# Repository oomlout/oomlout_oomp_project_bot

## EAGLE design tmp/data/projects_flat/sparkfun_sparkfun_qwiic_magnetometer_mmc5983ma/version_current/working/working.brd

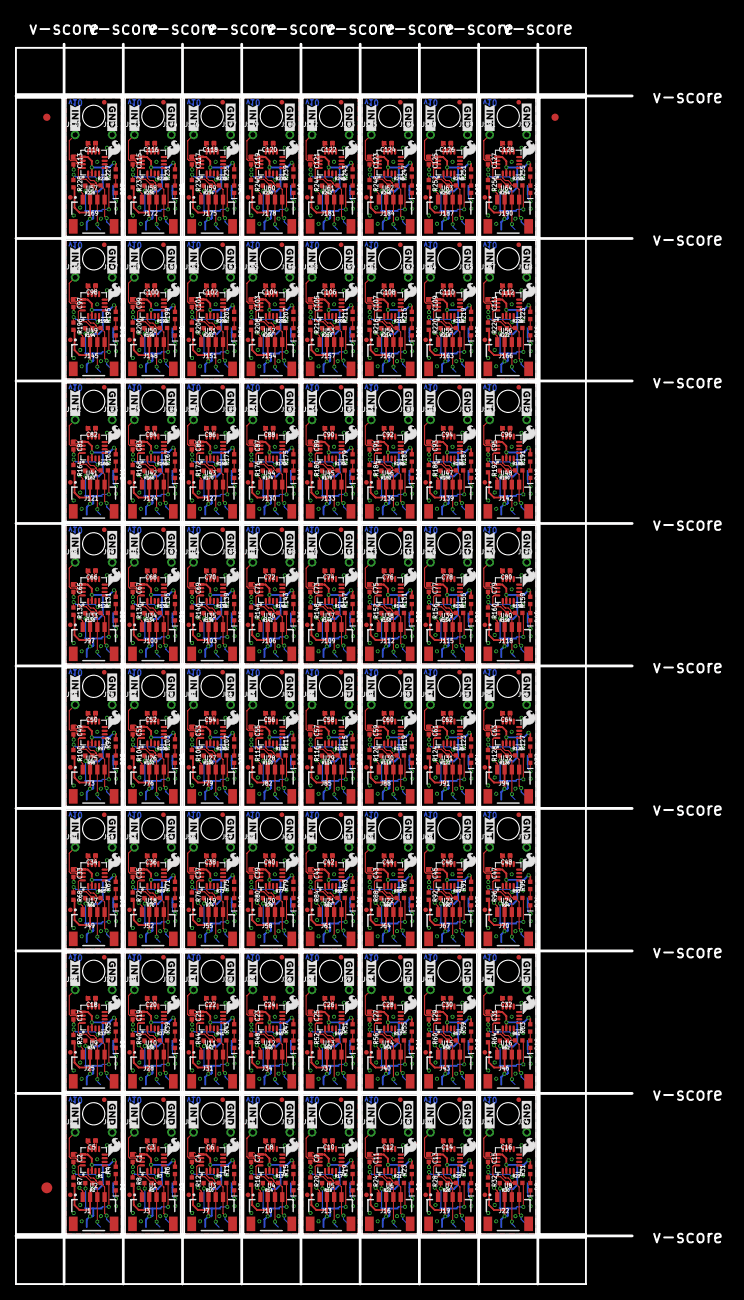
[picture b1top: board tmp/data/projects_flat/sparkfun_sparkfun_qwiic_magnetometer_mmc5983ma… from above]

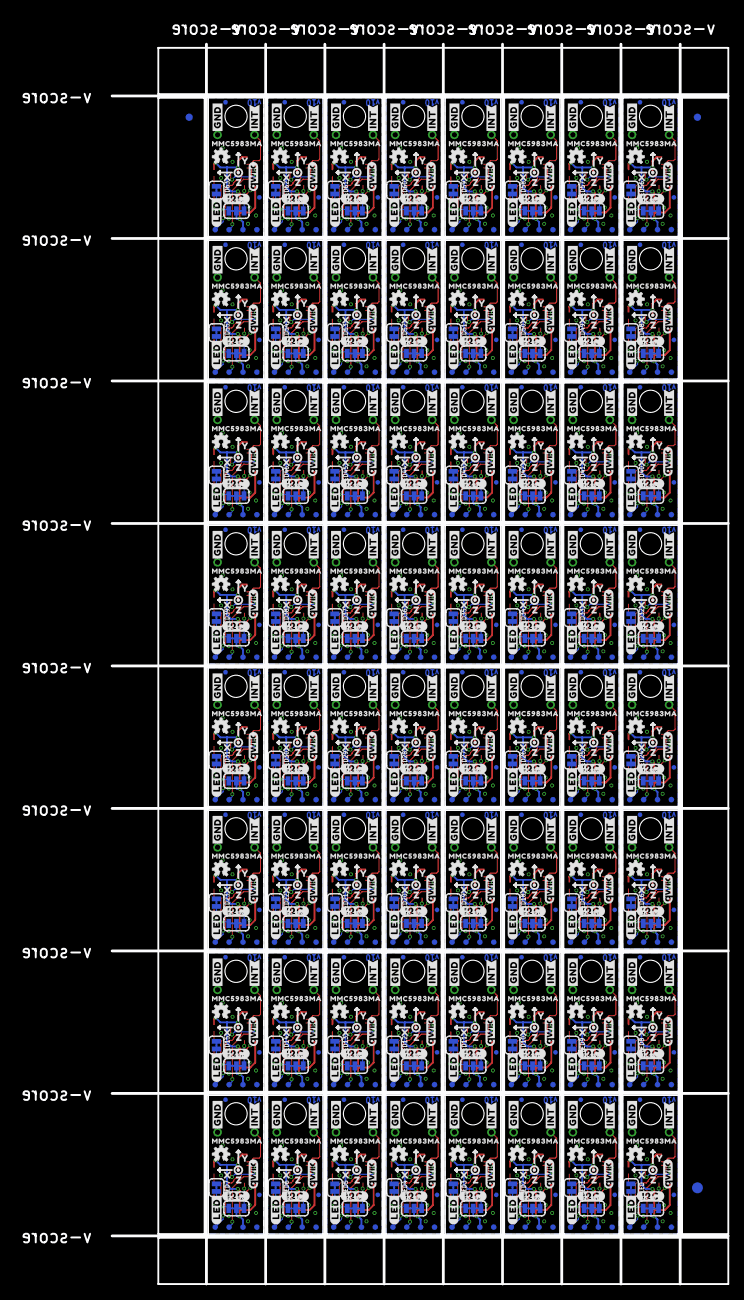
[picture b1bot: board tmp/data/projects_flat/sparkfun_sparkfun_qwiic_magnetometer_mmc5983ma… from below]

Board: 2 copper layers, 84.6 x 170.2 mm, 2374 parts (1155 on the bottom side), 704 nets.

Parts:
C1, C2, C4, C7, C9, C11, C13, C15, C17, C19, C21, C23, C25, C27, C29, C31, C33, C35, C37, C39, C41, C43, C45, C47, C49, C51, C53, C55, C57, C59, C61, C63, C65, C67, C69, C71, C73, C75, C77, C79, C81, C83, C85, C87, C89, C91, C93, C95, C97, C99, C101, C103, C105, C107, C109, C111, C113, C115, C117, C119, C121, C123, C125, C127: 1.0uF; 0402-TIGHT
C3, C5, C6, C8, C10, C12, C14, C16, C18, C20, C22, C24, C26, C28, C30, C32, C34, C36, C38, C40, C42, C44, C46, C48, C50, C52, C54, C56, C58, C60, C62, C64, C66, C68, C70, C72, C74, C76, C78, C80, C82, C84, C86, C88, C90, C92, C94, C96, C98, C100, C102, C104, C106, C108, C110, C112, C114, C116, C118, C120, C122, C124, C126, C128: 10uF; 0402-TIGHT
D1, D2, D3, D4, D5, D6, D7, D8, D9, D10, D11, D12, D13, D14, D15, D16, D17, D18, D19, D20, D21, D22, D23, D24, D25, D26, D27, D28, D29, D30, D31, D32, D33, D34, D35, D36, D37, D38, D39, D40, D41, D42, D43, D44, D45, D46, D47, D48, D49, D50, D51, D52, D53, D54, D55, D56, D57, D58, D59, D60, D61, D62, D63, D64: RED; LED-0402
E$1, E$2, E$3, E$4: FIDUCIAL-1X2
E$5, E$6: FIDUCIAL-1.5X3
FD1, FD2, FD3, FD4, FD5, FD6, FD7, FD8, FD9, FD10, FD11, FD12, FD13, FD14, FD15, FD16, FD17, FD18, FD19, FD20, FD21, FD22, FD23, FD24, FD25, FD26, FD27, FD28, FD29, FD30, FD31, FD32, FD33, FD34, FD35, FD36, FD37, FD38, FD39, FD40, FD41, FD42, FD43, FD44, FD45, FD46, FD47, FD48, FD49, FD50, FD51, FD52, FD53, FD54, FD55, FD56, FD57, FD58, FD59, FD60, FD61, FD62, FD63, FD64, FD65, FD66, FD67, FD68, FD69, FD70, FD71, FD72, FD73, FD74, FD75, FD76, FD77, FD78, FD79, FD80, FD81, FD82, FD83, FD84, FD85, FD86, FD87, FD88, FD89, FD90, FD91, FD92, FD93, FD94, FD95, FD96, FD97, FD98, FD99, FD100, FD101, FD102, FD103, FD104, FD105, FD106, FD107, FD108, FD109, FD110, FD111, FD112, FD113, FD114, FD115, FD116, FD117, FD118, FD119, FD120, FD121, FD122, FD123, FD124, FD125, FD126, FD127, FD128: FIDUCIALUFIDUCIAL; FIDUCIAL-MICRO
FID1, FID2, FID3, FID4, FID5, FID6, FID7, FID8, FID9, FID10, FID11, FID12, FID13, FID14, FID15, FID16, FID17, FID18, FID19, FID20, FID21, FID22, FID23, FID24, FID25, FID26, FID27, FID28, FID29, FID30, FID31, FID32, FID33, FID34, FID35, FID36, FID37, FID38, FID39, FID40, FID41, FID42, FID43, FID44, FID45, FID46, FID47, FID48, FID49, FID50, FID51, FID52, FID53, FID54, FID55, FID56, FID57, FID58, FID59, FID60, FID61, FID62, FID63, FID64, FID65, FID66, FID67, FID68, FID69, FID70, FID71, FID72, FID73, FID74, FID75, FID76, FID77, FID78, FID79, FID80, FID81, FID82, FID83, FID84, FID85, FID86, FID87, FID88, FID89, FID90, FID91, FID92, FID93, FID94, FID95, FID96, FID97, FID98, FID99, FID100, FID101, FID102, FID103, FID104, FID105, FID106, FID107, FID108, FID109, FID110, FID111, FID112, FID113, FID114, FID115, FID116, FID117, FID118, FID119, FID120, FID121, FID122, FID123, FID124, FID125, FID126, FID127, FID128: FIDUCIALUFIDUCIAL; FIDUCIAL-MICRO
FRAME1, FRAME2, FRAME3, FRAME4, FRAME5, FRAME6, FRAME7, FRAME8, FRAME9, FRAME10, FRAME11, FRAME12, FRAME13, FRAME14, FRAME15, FRAME16, FRAME17, FRAME18, FRAME19, FRAME20, FRAME21, FRAME22, FRAME23, FRAME24, FRAME25, FRAME26, FRAME27, FRAME28, FRAME29, FRAME30, FRAME31, FRAME32, FRAME33, FRAME34, FRAME35, FRAME36, FRAME37, FRAME38, FRAME39, FRAME40, FRAME41, FRAME42, FRAME43, FRAME44, FRAME45, FRAME46, FRAME47, FRAME48, FRAME49, FRAME50, FRAME51, FRAME52, FRAME53, FRAME54, FRAME55, FRAME56, FRAME57, FRAME58, FRAME59, FRAME60, FRAME61, FRAME62, FRAME63, FRAME64: FRAME-LETTER; CREATIVE_COMMONS
I2C_PU, I2C_PU1, I2C_PU2, I2C_PU3, I2C_PU4, I2C_PU5, I2C_PU6, I2C_PU7, I2C_PU8, I2C_PU9, I2C_PU10, I2C_PU11, I2C_PU12, I2C_PU13, I2C_PU14, I2C_PU15, I2C_PU16, I2C_PU17, I2C_PU18, I2C_PU19, I2C_PU20, I2C_PU21, I2C_PU22, I2C_PU23, I2C_PU24, I2C_PU25, I2C_PU26, I2C_PU27, I2C_PU28, I2C_PU29, I2C_PU30, I2C_PU31, I2C_PU32, I2C_PU33, I2C_PU34, I2C_PU35, I2C_PU36, I2C_PU37, I2C_PU38, I2C_PU39, I2C_PU40, I2C_PU41, I2C_PU42, I2C_PU43, I2C_PU44, I2C_PU45, I2C_PU46, I2C_PU47, I2C_PU48, I2C_PU49, I2C_PU50, I2C_PU51, I2C_PU52, I2C_PU53, I2C_PU54, I2C_PU55, I2C_PU56, I2C_PU57, I2C_PU58, I2C_PU59, I2C_PU60, I2C_PU61, I2C_PU62, I2C_PU63: S_MODE; SMT-JUMPER_3_2-NC_TRACE_SILK
J1, J3, J7, J10, J13, J16, J19, J22, J25, J28, J31, J34, J37, J40, J43, J46, J49, J52, J55, J58, J61, J64, J67, J70, J73, J76, J79, J82, J85, J88, J91, J94, J97, J100, J103, J106, J109, J112, J115, J118, J121, J124, J127, J130, J133, J136, J139, J142, J145, J148, J151, J154, J157, J160, J163, J166, J169, J172, J175, J178, J181, J184, J187, J190: QWIIC_RIGHT_ANGLE; JST04_1MM_RA
J2, J4, J5, J6, J8, J9, J11, J12, J14, J15, J17, J18, J20, J21, J23, J24, J26, J27, J29, J30, J32, J33, J35, J36, J38, J39, J41, J42, J44, J45, J47, J48, J50, J51, J53, J54, J56, J57, J59, J60, J62, J63, J65, J66, J68, J69, J71, J72, J74, J75, J77, J78, J80, J81, J83, J84, J86, J87, J89, J90, J92, J93, J95, J96, J98, J99, J101, J102, J104, J105, J107, J108, J110, J111, J113, J114, J116, J117, J119, J120, J122, J123, J125, J126, J128, J129, J131, J132, J134, J135, J137, J138, J140, J141, J143, J144, J146, J147, J149, J150, J152, J153, J155, J156, J158, J159, J161, J162, J164, J165, J167, J168, J170, J171, J173, J174, J176, J177, J179, J180, J182, J183, J185, J186, J188, J189, J191, J192: 1X01_1MM_NO_SILK
LED, LED1, LED2, LED3, LED4, LED5, LED6, LED7, LED8, LED9, LED10, LED11, LED12, LED13, LED14, LED15, LED16, LED17, LED18, LED19, LED20, LED21, LED22, LED23, LED24, LED25, LED26, LED27, LED28, LED29, LED30, LED31, LED32, LED33, LED34, LED35, LED36, LED37, LED38, LED39, LED40, LED41, LED42, LED43, LED44, LED45, LED46, LED47, LED48, LED49, LED50, LED51, LED52, LED53, LED54, LED55, LED56, LED57, LED58, LED59, LED60, LED61, LED62, LED63: JUMPER-SMT_2_NC_TRACE_SILK; SMT-JUMPER_2_NC_TRACE_SILK
LOGO1, LOGO5, LOGO8, LOGO11, LOGO14, LOGO17, LOGO20, LOGO23, LOGO26, LOGO29, LOGO32, LOGO35, LOGO38, LOGO41, LOGO44, LOGO47, LOGO50, LOGO53, LOGO56, LOGO59, LOGO62, LOGO65, LOGO68, LOGO71, LOGO74, LOGO77, LOGO80, LOGO83, LOGO86, LOGO89, LOGO92, LOGO95, LOGO98, LOGO101, LOGO104, LOGO107, LOGO110, LOGO113, LOGO116, LOGO119, LOGO122, LOGO125, LOGO128, LOGO131, LOGO134, LOGO137, LOGO140, LOGO143, LOGO146, LOGO149, LOGO152, LOGO155, LOGO158, LOGO161, LOGO164, LOGO167, LOGO170, LOGO173, LOGO176, LOGO179, LOGO182, LOGO185, LOGO188, LOGO191: QWIIC_LOGO_4MM; QWIIC_4MM
LOGO2, LOGO4, LOGO7, LOGO10, LOGO13, LOGO16, LOGO19, LOGO22, LOGO25, LOGO28, LOGO31, LOGO34, LOGO37, LOGO40, LOGO43, LOGO46, LOGO49, LOGO52, LOGO55, LOGO58, LOGO61, LOGO64, LOGO67, LOGO70, LOGO73, LOGO76, LOGO79, LOGO82, LOGO85, LOGO88, LOGO91, LOGO94, LOGO97, LOGO100, LOGO103, LOGO106, LOGO109, LOGO112, LOGO115, LOGO118, LOGO121, LOGO124, LOGO127, LOGO130, LOGO133, LOGO136, LOGO139, LOGO142, LOGO145, LOGO148, LOGO151, LOGO154, LOGO157, LOGO160, LOGO163, LOGO166, LOGO169, LOGO172, LOGO175, LOGO178, LOGO181, LOGO184, LOGO187, LOGO190: OSHW-LOGOMINI; OSHW-LOGO-MINI
LOGO3, LOGO6, LOGO9, LOGO12, LOGO15, LOGO18, LOGO21, LOGO24, LOGO27, LOGO30, LOGO33, LOGO36, LOGO39, LOGO42, LOGO45, LOGO48, LOGO51, LOGO54, LOGO57, LOGO60, LOGO63, LOGO66, LOGO69, LOGO72, LOGO75, LOGO78, LOGO81, LOGO84, LOGO87, LOGO90, LOGO93, LOGO96, LOGO99, LOGO102, LOGO105, LOGO108, LOGO111, LOGO114, LOGO117, LOGO120, LOGO123, LOGO126, LOGO129, LOGO132, LOGO135, LOGO138, LOGO141, LOGO144, LOGO147, LOGO150, LOGO153, LOGO156, LOGO159, LOGO162, LOGO165, LOGO168, LOGO171, LOGO174, LOGO177, LOGO180, LOGO183, LOGO186, LOGO189, LOGO192: SFE_LOGO_NAMEBLANK; BLANK
R1, R2, R3, R5, R9, R10, R13, R14, R17, R18, R21, R22, R25, R26, R29, R30, R33, R34, R37, R38, R41, R42, R45, R46, R49, R50, R53, R54, R57, R58, R61, R62, R65, R66, R69, R70, R73, R74, R77, R78, R81, R82, R85, R86, R89, R90, R93, R94, R97, R98, R101, R102, R105, R106, R109, R110, R113, R114, R117, R118, R121, R122, R125, R126, R129, R130, R133, R134, R137, R138, R141, R142, R145, R146, R149, R150, R153, R154, R157, R158, R161, R162, R165, R166, R169, R170, R173, R174, R177, R178, R181, R182, R185, R186, R189, R190, R193, R194, R197, R198, R201, R202, R205, R206, R209, R210, R213, R214, R217, R218, R221, R222, R225, R226, R229, R230, R233, R234, R237, R238, R241, R242, R245, R246, R249, R250, R253, R254: 2.2k; 0402-TIGHT
R4, R6, R11, R15, R19, R23, R27, R31, R35, R39, R43, R47, R51, R55, R59, R63, R67, R71, R75, R79, R83, R87, R91, R95, R99, R103, R107, R111, R115, R119, R123, R127, R131, R135, R139, R143, R147, R151, R155, R159, R163, R167, R171, R175, R179, R183, R187, R191, R195, R199, R203, R207, R211, R215, R219, R223, R227, R231, R235, R239, R243, R247, R251, R255: 1k; 0402-TIGHT
R7, R8, R12, R16, R20, R24, R28, R32, R36, R40, R44, R48, R52, R56, R60, R64, R68, R72, R76, R80, R84, R88, R92, R96, R100, R104, R108, R112, R116, R120, R124, R128, R132, R136, R140, R144, R148, R152, R156, R160, R164, R168, R172, R176, R180, R184, R188, R192, R196, R200, R204, R208, R212, R216, R220, R224, R228, R232, R236, R240, R244, R248, R252, R256: 100k; 0402-TIGHT
STANDOFF1, STANDOFF2, STANDOFF3, STANDOFF4, STANDOFF5, STANDOFF6, STANDOFF7, STANDOFF8, STANDOFF9, STANDOFF10, STANDOFF11, STANDOFF12, STANDOFF13, STANDOFF14, STANDOFF15, STANDOFF16, STANDOFF17, STANDOFF18, STANDOFF19, STANDOFF20, STANDOFF21, STANDOFF22, STANDOFF23, STANDOFF24, STANDOFF25, STANDOFF26, STANDOFF27, STANDOFF28, STANDOFF29, STANDOFF30, STANDOFF31, STANDOFF32, STANDOFF33, STANDOFF34, STANDOFF35, STANDOFF36, STANDOFF37, STANDOFF38, STANDOFF39, STANDOFF40, STANDOFF41, STANDOFF42, STANDOFF43, STANDOFF44, STANDOFF45, STANDOFF46, STANDOFF47, STANDOFF48, STANDOFF49, STANDOFF50, STANDOFF51, STANDOFF52, STANDOFF53, STANDOFF54, STANDOFF55, STANDOFF56, STANDOFF57, STANDOFF58, STANDOFF59, STANDOFF60, STANDOFF61, STANDOFF62, STANDOFF63, STANDOFF64: STAND-OFFTIGHT; STAND-OFF-TIGHT
TP1, TP2, TP3, TP4, TP5, TP6, TP7, TP8, TP9, TP10, TP11, TP12, TP13, TP14, TP15, TP16, TP17, TP18, TP19, TP20, TP21, TP22, TP23, TP24, TP25, TP26, TP27, TP28, TP29, TP30, TP31, TP32, TP33, TP34, TP35, TP36, TP37, TP38, TP39, TP40, TP41, TP42, TP43, TP44, TP45, TP46, TP47, TP48, TP49, TP50, TP51, TP52, TP53, TP54, TP55, TP56, TP57, TP58, TP59, TP60, TP61, TP62, TP63, TP64, TP65, TP66, TP67, TP68, TP69, TP70, TP71, TP72, TP73, TP74, TP75, TP76, TP77, TP78, TP79, TP80, TP81, TP82, TP83, TP84, TP85, TP86, TP87, TP88, TP89, TP90, TP91, TP92, TP93, TP94, TP95, TP96, TP97, TP98, TP99, TP100, TP101, TP102, TP103, TP104, TP105, TP106, TP107, TP108, TP109, TP110, TP111, TP112, TP113, TP114, TP115, TP116, TP117, TP118, TP119, TP120, TP121, TP122, TP123, TP124, TP125, TP126, TP127, TP128, TP129, TP130, TP131, TP132, TP133, TP134, TP135, TP136, TP137, TP138, TP139, TP140, TP141, TP142, TP143, TP144, TP145, TP146, TP147, TP148, TP149, TP150, TP151, TP152, TP153, TP154, TP155, TP156, TP157, TP158, TP159, TP160, TP161, TP162, TP163, TP164, TP165, TP166, TP167, TP168, TP169, TP170, TP171, TP172, TP173, TP174, TP175, TP176, TP177, TP178, TP179, TP180, TP181, TP182, TP183, TP184, TP185, TP186, TP187, TP188, TP189, TP190, TP191, TP192, TP193, TP194, TP195, TP196, TP197, TP198, TP199, TP200, TP201, TP202, TP203, TP204, TP205, TP206, TP207, TP208, TP209, TP210, TP211, TP212, TP213, TP214, TP215, TP216, TP217, TP218, TP219, TP220, TP221, TP222, TP223, TP224, TP225, TP226, TP227, TP228, TP229, TP230, TP231, TP232, TP233, TP234, TP235, TP236, TP237, TP238, TP239, TP240, TP241, TP242, TP243, TP244, TP245, TP246, TP247, TP248, TP249, TP250, TP251, TP252, TP253, TP254, TP255, TP256: TEST-POINT3; PAD.03X.03
U1, U2, U3, U4, U5, U6, U7, U8, U9, U10, U11, U12, U13, U14, U15, U16, U17, U18, U19, U20, U21, U22, U23, U24, U25, U26, U27, U28, U29, U30, U31, U32, U33, U34, U35, U36, U37, U38, U39, U40, U41, U42, U43, U44, U45, U46, U47, U48, U49, U50, U51, U52, U53, U54, U55, U56, U57, U58, U59, U60, U61, U62, U63, U64: MMC5983MA_QFN16; LGA-16-3X3MM-4X4PINS
U$1, U$18, U$30, U$41, U$52, U$63, U$74, U$85, U$96, U$107, U$118, U$129, U$140, U$151, U$162, U$173, U$184, U$195, U$206, U$217, U$228, U$239, U$250, U$261, U$272, U$283, U$294, U$305, U$316, U$327, U$338, U$349, U$360, U$371, U$382, U$393, U$404, U$415, U$426, U$437, U$448, U$459, U$470, U$481, U$492, U$503, U$514, U$525, U$536, U$547, U$558, U$569, U$580, U$591, U$602, U$613, U$624, U$635, U$646, U$657, U$668, U$679, U$690, U$701: #INT#20
U$2, U$15, U$26, U$38, U$49, U$60, U$71, U$82, U$93, U$104, U$115, U$126, U$137, U$148, U$159, U$170, U$181, U$192, U$203, U$214, U$225, U$236, U$247, U$258, U$269, U$280, U$291, U$302, U$313, U$324, U$335, U$346, U$357, U$368, U$379, U$390, U$401, U$412, U$423, U$434, U$445, U$456, U$467, U$478, U$489, U$500, U$511, U$522, U$533, U$544, U$555, U$566, U$577, U$588, U$599, U$610, U$621, U$632, U$643, U$654, U$665, U$676, U$687, U$698: MMC5983MA331
U$3, U$16, U$27, U$39, U$50, U$61, U$72, U$83, U$94, U$105, U$116, U$127, U$138, U$149, U$160, U$171, U$182, U$193, U$204, U$215, U$226, U$237, U$248, U$259, U$270, U$281, U$292, U$303, U$314, U$325, U$336, U$347, U$358, U$369, U$380, U$391, U$402, U$413, U$424, U$435, U$446, U$457, U$468, U$479, U$490, U$501, U$512, U$523, U$534, U$545, U$556, U$567, U$578, U$589, U$600, U$611, U$622, U$633, U$644, U$655, U$666, U$677, U$688, U$699: #I2C#4
U$4, U$6, U$19, U$21, U$31, U$33, U$42, U$44, U$53, U$55, U$64, U$66, U$75, U$77, U$86, U$88, U$97, U$99, U$108, U$110, U$119, U$121, U$130, U$132, U$141, U$143, U$152, U$154, U$163, U$165, U$174, U$176, U$185, U$187, U$196, U$198, U$207, U$209, U$218, U$220, U$229, U$231, U$240, U$242, U$251, U$253, U$262, U$264, U$273, U$275, U$284, U$286, U$295, U$297, U$306, U$308, U$317, U$319, U$328, U$330, U$339, U$341, U$350, U$352, U$361, U$363, U$372, U$374, U$383, U$385, U$394, U$396, U$405, U$407, U$416, U$418, U$427, U$429, U$438, U$440, U$449, U$451, U$460, U$462, U$471, U$473, U$482, U$484, U$493, U$495, U$504, U$506, U$515, U$517, U$526, U$528, U$537, U$539, U$548, U$550, U$559, U$561, U$570, U$572, U$581, U$583, U$592, U$594, U$603, U$605, U$614, U$616, U$625, U$627, U$636, U$638, U$647, U$649, U$658, U$660, U$669, U$671, U$680, U$682, U$691, U$693, U$702, U$704: #GND#4
U$5, U$20, U$32, U$43, U$54, U$65, U$76, U$87, U$98, U$109, U$120, U$131, U$142, U$153, U$164, U$175, U$186, U$197, U$208, U$219, U$230, U$241, U$252, U$263, U$274, U$285, U$296, U$307, U$318, U$329, U$340, U$351, U$362, U$373, U$384, U$395, U$406, U$417, U$428, U$439, U$450, U$461, U$472, U$483, U$494, U$505, U$516, U$527, U$538, U$549, U$560, U$571, U$582, U$593, U$604, U$615, U$626, U$637, U$648, U$659, U$670, U$681, U$692, U$703: #INT#21
U$7, U$22, U$29, U$34, U$45, U$56, U$67, U$78, U$89, U$100, U$111, U$122, U$133, U$144, U$155, U$166, U$177, U$188, U$199, U$210, U$221, U$232, U$243, U$254, U$265, U$276, U$287, U$298, U$309, U$320, U$331, U$342, U$353, U$364, U$375, U$386, U$397, U$408, U$419, U$430, U$441, U$452, U$463, U$474, U$485, U$496, U$507, U$518, U$529, U$540, U$551, U$562, U$573, U$584, U$595, U$606, U$617, U$628, U$639, U$650, U$661, U$672, U$683, U$694: SFE_LOGO_FLAME_.1
U$8, U$12, U$23, U$35, U$46, U$57, U$68, U$79, U$90, U$101, U$112, U$123, U$134, U$145, U$156, U$167, U$178, U$189, U$200, U$211, U$222, U$233, U$244, U$255, U$266, U$277, U$288, U$299, U$310, U$321, U$332, U$343, U$354, U$365, U$376, U$387, U$398, U$409, U$420, U$431, U$442, U$453, U$464, U$475, U$486, U$497, U$508, U$519, U$530, U$541, U$552, U$563, U$574, U$585, U$596, U$607, U$618, U$629, U$640, U$651, U$662, U$673, U$684, U$695: X2114
U$9, U$13, U$24, U$36, U$47, U$58, U$69, U$80, U$91, U$102, U$113, U$124, U$135, U$146, U$157, U$168, U$179, U$190, U$201, U$212, U$223, U$234, U$245, U$256, U$267, U$278, U$289, U$300, U$311, U$322, U$333, U$344, U$355, U$366, U$377, U$388, U$399, U$410, U$421, U$432, U$443, U$454, U$465, U$476, U$487, U$498, U$509, U$520, U$531, U$542, U$553, U$564, U$575, U$586, U$597, U$608, U$619, U$630, U$641, U$652, U$663, U$674, U$685, U$696: Y2115
U$10, U$14, U$25, U$37, U$48, U$59, U$70, U$81, U$92, U$103, U$114, U$125, U$136, U$147, U$158, U$169, U$180, U$191, U$202, U$213, U$224, U$235, U$246, U$257, U$268, U$279, U$290, U$301, U$312, U$323, U$334, U$345, U$356, U$367, U$378, U$389, U$400, U$411, U$422, U$433, U$444, U$455, U$466, U$477, U$488, U$499, U$510, U$521, U$532, U$543, U$554, U$565, U$576, U$587, U$598, U$609, U$620, U$631, U$642, U$653, U$664, U$675, U$686, U$697: Z2116
U$11, U$17, U$28, U$40, U$51, U$62, U$73, U$84, U$95, U$106, U$117, U$128, U$139, U$150, U$161, U$172, U$183, U$194, U$205, U$216, U$227, U$238, U$249, U$260, U$271, U$282, U$293, U$304, U$315, U$326, U$337, U$348, U$359, U$370, U$381, U$392, U$403, U$414, U$425, U$436, U$447, U$458, U$469, U$480, U$491, U$502, U$513, U$524, U$535, U$546, U$557, U$568, U$579, U$590, U$601, U$612, U$623, U$634, U$645, U$656, U$667, U$678, U$689, U$700: #LED#5

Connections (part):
3.3V: C2.1, I2C_PU.2, J1.2, R4.2, R7.2, TP1.1, U2.2, U2.13
3.3V1: C1.1, I2C_PU1.2, J3.2, R6.2, R8.2, TP4.1, U1.2, U1.13
3.3V2: C4.1, I2C_PU2.2, J7.2, R11.2, R12.2, TP9.1, U3.2, U3.13
3.3V3: C7.1, I2C_PU3.2, J10.2, R15.2, R16.2, TP13.1, U4.2, U4.13
3.3V4: C9.1, I2C_PU4.2, J13.2, R19.2, R20.2, TP17.1, U5.2, U5.13
3.3V5: C11.1, I2C_PU5.2, J16.2, R23.2, R24.2, TP21.1, U6.2, U6.13
3.3V6: C13.1, I2C_PU6.2, J19.2, R27.2, R28.2, TP25.1, U7.2, U7.13
3.3V7: C15.1, I2C_PU7.2, J22.2, R31.2, R32.2, TP29.1, U8.2, U8.13
3.3V8: C17.1, I2C_PU8.2, J25.2, R35.2, R36.2, TP33.1, U9.2, U9.13
3.3V9: C19.1, I2C_PU9.2, J28.2, R39.2, R40.2, TP37.1, U10.2, U10.13
3.3V10: C21.1, I2C_PU10.2, J31.2, R43.2, R44.2, TP41.1, U11.2, U11.13
3.3V11: C23.1, I2C_PU11.2, J34.2, R47.2, R48.2, TP45.1, U12.2, U12.13
3.3V12: C25.1, I2C_PU12.2, J37.2, R51.2, R52.2, TP49.1, U13.2, U13.13
3.3V13: C27.1, I2C_PU13.2, J40.2, R55.2, R56.2, TP53.1, U14.2, U14.13
3.3V14: C29.1, I2C_PU14.2, J43.2, R59.2, R60.2, TP57.1, U15.2, U15.13
3.3V15: C31.1, I2C_PU15.2, J46.2, R63.2, R64.2, TP61.1, U16.2, U16.13
3.3V16: C33.1, I2C_PU16.2, J49.2, R67.2, R68.2, TP65.1, U17.2, U17.13
3.3V17: C35.1, I2C_PU17.2, J52.2, R71.2, R72.2, TP69.1, U18.2, U18.13
3.3V18: C37.1, I2C_PU18.2, J55.2, R75.2, R76.2, TP73.1, U19.2, U19.13
3.3V19: C39.1, I2C_PU19.2, J58.2, R79.2, R80.2, TP77.1, U20.2, U20.13
3.3V20: C41.1, I2C_PU20.2, J61.2, R83.2, R84.2, TP81.1, U21.2, U21.13
3.3V21: C43.1, I2C_PU21.2, J64.2, R87.2, R88.2, TP85.1, U22.2, U22.13
3.3V22: C45.1, I2C_PU22.2, J67.2, R91.2, R92.2, TP89.1, U23.2, U23.13
3.3V23: C47.1, I2C_PU23.2, J70.2, R95.2, R96.2, TP93.1, U24.2, U24.13
3.3V24: C49.1, I2C_PU24.2, J73.2, R99.2, R100.2, TP97.1, U25.2, U25.13
3.3V25: C51.1, I2C_PU25.2, J76.2, R103.2, R104.2, TP101.1, U26.2, U26.13
3.3V26: C53.1, I2C_PU26.2, J79.2, R107.2, R108.2, TP105.1, U27.2, U27.13
3.3V27: C55.1, I2C_PU27.2, J82.2, R111.2, R112.2, TP109.1, U28.2, U28.13
3.3V28: C57.1, I2C_PU28.2, J85.2, R115.2, R116.2, TP113.1, U29.2, U29.13
3.3V29: C59.1, I2C_PU29.2, J88.2, R119.2, R120.2, TP117.1, U30.2, U30.13
3.3V30: C61.1, I2C_PU30.2, J91.2, R123.2, R124.2, TP121.1, U31.2, U31.13
3.3V31: C63.1, I2C_PU31.2, J94.2, R127.2, R128.2, TP125.1, U32.2, U32.13
3.3V32: C65.1, I2C_PU32.2, J97.2, R131.2, R132.2, TP129.1, U33.2, U33.13
3.3V33: C67.1, I2C_PU33.2, J100.2, R135.2, R136.2, TP133.1, U34.2, U34.13
3.3V34: C69.1, I2C_PU34.2, J103.2, R139.2, R140.2, TP137.1, U35.2, U35.13
3.3V35: C71.1, I2C_PU35.2, J106.2, R143.2, R144.2, TP141.1, U36.2, U36.13
3.3V36: C73.1, I2C_PU36.2, J109.2, R147.2, R148.2, TP145.1, U37.2, U37.13
3.3V37: C75.1, I2C_PU37.2, J112.2, R151.2, R152.2, TP149.1, U38.2, U38.13
3.3V38: C77.1, I2C_PU38.2, J115.2, R155.2, R156.2, TP153.1, U39.2, U39.13
3.3V39: C79.1, I2C_PU39.2, J118.2, R159.2, R160.2, TP157.1, U40.2, U40.13
3.3V40: C81.1, I2C_PU40.2, J121.2, R163.2, R164.2, TP161.1, U41.2, U41.13
3.3V41: C83.1, I2C_PU41.2, J124.2, R167.2, R168.2, TP165.1, U42.2, U42.13
3.3V42: C85.1, I2C_PU42.2, J127.2, R171.2, R172.2, TP169.1, U43.2, U43.13
3.3V43: C87.1, I2C_PU43.2, J130.2, R175.2, R176.2, TP173.1, U44.2, U44.13
3.3V44: C89.1, I2C_PU44.2, J133.2, R179.2, R180.2, TP177.1, U45.2, U45.13
3.3V45: C91.1, I2C_PU45.2, J136.2, R183.2, R184.2, TP181.1, U46.2, U46.13
3.3V46: C93.1, I2C_PU46.2, J139.2, R187.2, R188.2, TP185.1, U47.2, U47.13
3.3V47: C95.1, I2C_PU47.2, J142.2, R191.2, R192.2, TP189.1, U48.2, U48.13
3.3V48: C97.1, I2C_PU48.2, J145.2, R195.2, R196.2, TP193.1, U49.2, U49.13
3.3V49: C99.1, I2C_PU49.2, J148.2, R199.2, R200.2, TP197.1, U50.2, U50.13
3.3V50: C101.1, I2C_PU50.2, J151.2, R203.2, R204.2, TP201.1, U51.2, U51.13
3.3V51: C103.1, I2C_PU51.2, J154.2, R207.2, R208.2, TP205.1, U52.2, U52.13
3.3V52: C105.1, I2C_PU52.2, J157.2, R211.2, R212.2, TP209.1, U53.2, U53.13
3.3V53: C107.1, I2C_PU53.2, J160.2, R215.2, R216.2, TP213.1, U54.2, U54.13
3.3V54: C109.1, I2C_PU54.2, J163.2, R219.2, R220.2, TP217.1, U55.2, U55.13
3.3V55: C111.1, I2C_PU55.2, J166.2, R223.2, R224.2, TP221.1, U56.2, U56.13
3.3V56: C113.1, I2C_PU56.2, J169.2, R227.2, R228.2, TP225.1, U57.2, U57.13
3.3V57: C115.1, I2C_PU57.2, J172.2, R231.2, R232.2, TP229.1, U58.2, U58.13
3.3V58: C117.1, I2C_PU58.2, J175.2, R235.2, R236.2, TP233.1, U59.2, U59.13
3.3V59: C119.1, I2C_PU59.2, J178.2, R239.2, R240.2, TP237.1, U60.2, U60.13
3.3V60: C121.1, I2C_PU60.2, J181.2, R243.2, R244.2, TP241.1, U61.2, U61.13
3.3V61: C123.1, I2C_PU61.2, J184.2, R247.2, R248.2, TP245.1, U62.2, U62.13
3.3V62: C125.1, I2C_PU62.2, J187.2, R251.2, R252.2, TP249.1, U63.2, U63.13
3.3V63: C127.1, I2C_PU63.2, J190.2, R255.2, R256.2, TP253.1, U64.2, U64.13
!MAG_CS!: R7.1, U2.4
!MAG_CS!1: R8.1, U1.4
!MAG_CS!2: R12.1, U3.4
!MAG_CS!3: R16.1, U4.4
!MAG_CS!4: R20.1, U5.4
!MAG_CS!5: R24.1, U6.4
!MAG_CS!6: R28.1, U7.4
!MAG_CS!7: R32.1, U8.4
!MAG_CS!8: R36.1, U9.4
!MAG_CS!9: R40.1, U10.4
!MAG_CS!10: R44.1, U11.4
!MAG_CS!11: R48.1, U12.4
!MAG_CS!12: R52.1, U13.4
!MAG_CS!13: R56.1, U14.4
!MAG_CS!14: R60.1, U15.4
!MAG_CS!15: R64.1, U16.4
!MAG_CS!16: R68.1, U17.4
!MAG_CS!17: R72.1, U18.4
!MAG_CS!18: R76.1, U19.4
!MAG_CS!19: R80.1, U20.4
!MAG_CS!20: R84.1, U21.4
!MAG_CS!21: R88.1, U22.4
!MAG_CS!22: R92.1, U23.4
!MAG_CS!23: R96.1, U24.4
!MAG_CS!24: R100.1, U25.4
!MAG_CS!25: R104.1, U26.4
!MAG_CS!26: R108.1, U27.4
!MAG_CS!27: R112.1, U28.4
!MAG_CS!28: R116.1, U29.4
!MAG_CS!29: R120.1, U30.4
!MAG_CS!30: R124.1, U31.4
!MAG_CS!31: R128.1, U32.4
!MAG_CS!32: R132.1, U33.4
!MAG_CS!33: R136.1, U34.4
!MAG_CS!34: R140.1, U35.4
!MAG_CS!35: R144.1, U36.4
!MAG_CS!36: R148.1, U37.4
!MAG_CS!37: R152.1, U38.4
!MAG_CS!38: R156.1, U39.4
!MAG_CS!39: R160.1, U40.4
!MAG_CS!40: R164.1, U41.4
!MAG_CS!41: R168.1, U42.4
!MAG_CS!42: R172.1, U43.4
!MAG_CS!43: R176.1, U44.4
!MAG_CS!44: R180.1, U45.4
!MAG_CS!45: R184.1, U46.4
!MAG_CS!46: R188.1, U47.4
!MAG_CS!47: R192.1, U48.4
!MAG_CS!48: R196.1, U49.4
!MAG_CS!49: R200.1, U50.4
!MAG_CS!50: R204.1, U51.4
!MAG_CS!51: R208.1, U52.4
!MAG_CS!52: R212.1, U53.4
!MAG_CS!53: R216.1, U54.4
!MAG_CS!54: R220.1, U55.4
!MAG_CS!55: R224.1, U56.4
!MAG_CS!56: R228.1, U57.4
!MAG_CS!57: R232.1, U58.4
!MAG_CS!58: R236.1, U59.4
!MAG_CS!59: R240.1, U60.4
!MAG_CS!60: R244.1, U61.4
!MAG_CS!61: R248.1, U62.4
!MAG_CS!62: R252.1, U63.4
!MAG_CS!63: R256.1, U64.4
CAP: C5.1, U2.10
CAP1: C3.1, U1.10
CAP2: C6.1, U3.10
CAP3: C8.1, U4.10
CAP4: C10.1, U5.10
CAP5: C12.1, U6.10
CAP6: C14.1, U7.10
CAP7: C16.1, U8.10
CAP8: C18.1, U9.10
CAP9: C20.1, U10.10
CAP10: C22.1, U11.10
CAP11: C24.1, U12.10
CAP12: C26.1, U13.10
CAP13: C28.1, U14.10
CAP14: C30.1, U15.10
CAP15: C32.1, U16.10
CAP16: C34.1, U17.10
CAP17: C36.1, U18.10
CAP18: C38.1, U19.10
CAP19: C40.1, U20.10
CAP20: C42.1, U21.10
CAP21: C44.1, U22.10
CAP22: C46.1, U23.10
CAP23: C48.1, U24.10
CAP24: C50.1, U25.10
CAP25: C52.1, U26.10
CAP26: C54.1, U27.10
CAP27: C56.1, U28.10
CAP28: C58.1, U29.10
CAP29: C60.1, U30.10
CAP30: C62.1, U31.10
CAP31: C64.1, U32.10
CAP32: C66.1, U33.10
CAP33: C68.1, U34.10
CAP34: C70.1, U35.10
CAP35: C72.1, U36.10
CAP36: C74.1, U37.10
CAP37: C76.1, U38.10
CAP38: C78.1, U39.10
CAP39: C80.1, U40.10
CAP40: C82.1, U41.10
CAP41: C84.1, U42.10
CAP42: C86.1, U43.10
CAP43: C88.1, U44.10
CAP44: C90.1, U45.10
CAP45: C92.1, U46.10
CAP46: C94.1, U47.10
CAP47: C96.1, U48.10
CAP48: C98.1, U49.10
CAP49: C100.1, U50.10
CAP50: C102.1, U51.10
CAP51: C104.1, U52.10
CAP52: C106.1, U53.10
CAP53: C108.1, U54.10
CAP54: C110.1, U55.10
CAP55: C112.1, U56.10
CAP56: C114.1, U57.10
CAP57: C116.1, U58.10
CAP58: C118.1, U59.10
CAP59: C120.1, U60.10
CAP60: C122.1, U61.10
CAP61: C124.1, U62.10
CAP62: C126.1, U63.10
CAP63: C128.1, U64.10
GND: C2.2, C5.2, J1.1, J4.1, LED.1, TP5.1, U2.9, U2.11
GND1: C1.2, C3.2, J3.1, J6.1, LED1.1, TP8.1, U1.9, U1.11
GND2: C4.2, C6.2, J7.1, J9.1, LED2.1, TP12.1, U3.9, U3.11
GND3: C7.2, C8.2, J10.1, J12.1, LED3.1, TP16.1, U4.9, U4.11
GND4: C9.2, C10.2, J13.1, J15.1, LED4.1, TP20.1, U5.9, U5.11
GND5: C11.2, C12.2, J16.1, J18.1, LED5.1, TP24.1, U6.9, U6.11
GND6: C13.2, C14.2, J19.1, J21.1, LED6.1, TP28.1, U7.9, U7.11
GND7: C15.2, C16.2, J22.1, J24.1, LED7.1, TP32.1, U8.9, U8.11
GND8: C17.2, C18.2, J25.1, J27.1, LED8.1, TP36.1, U9.9, U9.11
GND9: C19.2, C20.2, J28.1, J30.1, LED9.1, TP40.1, U10.9, U10.11
GND10: C21.2, C22.2, J31.1, J33.1, LED10.1, TP44.1, U11.9, U11.11
GND11: C23.2, C24.2, J34.1, J36.1, LED11.1, TP48.1, U12.9, U12.11
GND12: C25.2, C26.2, J37.1, J39.1, LED12.1, TP52.1, U13.9, U13.11
GND13: C27.2, C28.2, J40.1, J42.1, LED13.1, TP56.1, U14.9, U14.11
GND14: C29.2, C30.2, J43.1, J45.1, LED14.1, TP60.1, U15.9, U15.11
GND15: C31.2, C32.2, J46.1, J48.1, LED15.1, TP64.1, U16.9, U16.11
GND16: C33.2, C34.2, J49.1, J51.1, LED16.1, TP68.1, U17.9, U17.11
GND17: C35.2, C36.2, J52.1, J54.1, LED17.1, TP72.1, U18.9, U18.11
GND18: C37.2, C38.2, J55.1, J57.1, LED18.1, TP76.1, U19.9, U19.11
GND19: C39.2, C40.2, J58.1, J60.1, LED19.1, TP80.1, U20.9, U20.11
GND20: C41.2, C42.2, J61.1, J63.1, LED20.1, TP84.1, U21.9, U21.11
GND21: C43.2, C44.2, J64.1, J66.1, LED21.1, TP88.1, U22.9, U22.11
GND22: C45.2, C46.2, J67.1, J69.1, LED22.1, TP92.1, U23.9, U23.11
GND23: C47.2, C48.2, J70.1, J72.1, LED23.1, TP96.1, U24.9, U24.11
GND24: C49.2, C50.2, J73.1, J75.1, LED24.1, TP100.1, U25.9, U25.11
GND25: C51.2, C52.2, J76.1, J78.1, LED25.1, TP104.1, U26.9, U26.11
GND26: C53.2, C54.2, J79.1, J81.1, LED26.1, TP108.1, U27.9, U27.11
GND27: C55.2, C56.2, J82.1, J84.1, LED27.1, TP112.1, U28.9, U28.11
GND28: C57.2, C58.2, J85.1, J87.1, LED28.1, TP116.1, U29.9, U29.11
GND29: C59.2, C60.2, J88.1, J90.1, LED29.1, TP120.1, U30.9, U30.11
GND30: C61.2, C62.2, J91.1, J93.1, LED30.1, TP124.1, U31.9, U31.11
GND31: C63.2, C64.2, J94.1, J96.1, LED31.1, TP128.1, U32.9, U32.11
GND32: C65.2, C66.2, J97.1, J99.1, LED32.1, TP132.1, U33.9, U33.11
GND33: C67.2, C68.2, J100.1, J102.1, LED33.1, TP136.1, U34.9, U34.11
GND34: C69.2, C70.2, J103.1, J105.1, LED34.1, TP140.1, U35.9, U35.11
GND35: C71.2, C72.2, J106.1, J108.1, LED35.1, TP144.1, U36.9, U36.11
GND36: C73.2, C74.2, J109.1, J111.1, LED36.1, TP148.1, U37.9, U37.11
GND37: C75.2, C76.2, J112.1, J114.1, LED37.1, TP152.1, U38.9, U38.11
GND38: C77.2, C78.2, J115.1, J117.1, LED38.1, TP156.1, U39.9, U39.11
GND39: C79.2, C80.2, J118.1, J120.1, LED39.1, TP160.1, U40.9, U40.11
GND40: C81.2, C82.2, J121.1, J123.1, LED40.1, TP164.1, U41.9, U41.11
GND41: C83.2, C84.2, J124.1, J126.1, LED41.1, TP168.1, U42.9, U42.11
GND42: C85.2, C86.2, J127.1, J129.1, LED42.1, TP172.1, U43.9, U43.11
GND43: C87.2, C88.2, J130.1, J132.1, LED43.1, TP176.1, U44.9, U44.11
GND44: C89.2, C90.2, J133.1, J135.1, LED44.1, TP180.1, U45.9, U45.11
GND45: C91.2, C92.2, J136.1, J138.1, LED45.1, TP184.1, U46.9, U46.11
GND46: C93.2, C94.2, J139.1, J141.1, LED46.1, TP188.1, U47.9, U47.11
GND47: C95.2, C96.2, J142.1, J144.1, LED47.1, TP192.1, U48.9, U48.11
GND48: C97.2, C98.2, J145.1, J147.1, LED48.1, TP196.1, U49.9, U49.11
GND49: C99.2, C100.2, J148.1, J150.1, LED49.1, TP200.1, U50.9, U50.11
GND50: C101.2, C102.2, J151.1, J153.1, LED50.1, TP204.1, U51.9, U51.11
GND51: C103.2, C104.2, J154.1, J156.1, LED51.1, TP208.1, U52.9, U52.11
GND52: C105.2, C106.2, J157.1, J159.1, LED52.1, TP212.1, U53.9, U53.11
GND53: C107.2, C108.2, J160.1, J162.1, LED53.1, TP216.1, U54.9, U54.11
GND54: C109.2, C110.2, J163.1, J165.1, LED54.1, TP220.1, U55.9, U55.11
GND55: C111.2, C112.2, J166.1, J168.1, LED55.1, TP224.1, U56.9, U56.11
GND56: C113.2, C114.2, J169.1, J171.1, LED56.1, TP228.1, U57.9, U57.11
GND57: C115.2, C116.2, J172.1, J174.1, LED57.1, TP232.1, U58.9, U58.11
GND58: C117.2, C118.2, J175.1, J177.1, LED58.1, TP236.1, U59.9, U59.11
GND59: C119.2, C120.2, J178.1, J180.1, LED59.1, TP240.1, U60.9, U60.11
GND60: C121.2, C122.2, J181.1, J183.1, LED60.1, TP244.1, U61.9, U61.11
GND61: C123.2, C124.2, J184.1, J186.1, LED61.1, TP248.1, U62.9, U62.11
GND62: C125.2, C126.2, J187.1, J189.1, LED62.1, TP252.1, U63.9, U63.11
GND63: C127.2, C128.2, J190.1, J192.1, LED63.1, TP256.1, U64.9, U64.11
INT: J2.1, U2.15
INT1: J5.1, U1.15
INT2: J8.1, U3.15
INT3: J11.1, U4.15
INT4: J14.1, U5.15
INT5: J17.1, U6.15
INT6: J20.1, U7.15
INT7: J23.1, U8.15
INT8: J26.1, U9.15
INT9: J29.1, U10.15
INT10: J32.1, U11.15
INT11: J35.1, U12.15
INT12: J38.1, U13.15
INT13: J41.1, U14.15
INT14: J44.1, U15.15
INT15: J47.1, U16.15
INT16: J50.1, U17.15
INT17: J53.1, U18.15
INT18: J56.1, U19.15
INT19: J59.1, U20.15
INT20: J62.1, U21.15
INT21: J65.1, U22.15
INT22: J68.1, U23.15
INT23: J71.1, U24.15
INT24: J74.1, U25.15
INT25: J77.1, U26.15
INT26: J80.1, U27.15
INT27: J83.1, U28.15
INT28: J86.1, U29.15
INT29: J89.1, U30.15
INT30: J92.1, U31.15
INT31: J95.1, U32.15
INT32: J98.1, U33.15
INT33: J101.1, U34.15
INT34: J104.1, U35.15
INT35: J107.1, U36.15
INT36: J110.1, U37.15
INT37: J113.1, U38.15
INT38: J116.1, U39.15
INT39: J119.1, U40.15
INT40: J122.1, U41.15
INT41: J125.1, U42.15
INT42: J128.1, U43.15
INT43: J131.1, U44.15
INT44: J134.1, U45.15
INT45: J137.1, U46.15
INT46: J140.1, U47.15
INT47: J143.1, U48.15
INT48: J146.1, U49.15
INT49: J149.1, U50.15
INT50: J152.1, U51.15
INT51: J155.1, U52.15
INT52: J158.1, U53.15
INT53: J161.1, U54.15
INT54: J164.1, U55.15
INT55: J167.1, U56.15
INT56: J170.1, U57.15
INT57: J173.1, U58.15
INT58: J176.1, U59.15
INT59: J179.1, U60.15
INT60: J182.1, U61.15
INT61: J185.1, U62.15
INT62: J188.1, U63.15
INT63: J191.1, U64.15
unnamed: I2C_PU1.1, R3.2
unnamed: D1.A, R4.1
unnamed: D1.C, LED.2
unnamed: I2C_PU1.3, R5.2
unnamed: I2C_PU.1, R1.2
unnamed: I2C_PU.3, R2.2
unnamed: D2.A, R6.1
unnamed: D2.C, LED1.2
unnamed: I2C_PU2.1, R9.2
unnamed: I2C_PU2.3, R10.2
unnamed: D3.A, R11.1
unnamed: D3.C, LED2.2
unnamed: I2C_PU3.1, R13.2
unnamed: I2C_PU3.3, R14.2
unnamed: D4.A, R15.1
unnamed: D4.C, LED3.2
unnamed: I2C_PU4.1, R17.2
unnamed: I2C_PU4.3, R18.2
unnamed: D5.A, R19.1
unnamed: D5.C, LED4.2
unnamed: I2C_PU5.1, R21.2
unnamed: I2C_PU5.3, R22.2
unnamed: D6.A, R23.1
unnamed: D6.C, LED5.2
unnamed: I2C_PU6.1, R25.2
unnamed: I2C_PU6.3, R26.2
unnamed: D7.A, R27.1
unnamed: D7.C, LED6.2
unnamed: I2C_PU7.1, R29.2
unnamed: I2C_PU7.3, R30.2
unnamed: D8.A, R31.1
unnamed: D8.C, LED7.2
unnamed: I2C_PU8.1, R33.2
unnamed: I2C_PU8.3, R34.2
unnamed: D9.A, R35.1
unnamed: D9.C, LED8.2
unnamed: I2C_PU9.1, R37.2
unnamed: I2C_PU9.3, R38.2
unnamed: D10.A, R39.1
unnamed: D10.C, LED9.2
unnamed: I2C_PU10.1, R41.2
unnamed: I2C_PU10.3, R42.2
unnamed: D11.A, R43.1
unnamed: D11.C, LED10.2
unnamed: I2C_PU11.1, R45.2
unnamed: I2C_PU11.3, R46.2
unnamed: D12.A, R47.1
unnamed: D12.C, LED11.2
unnamed: I2C_PU12.1, R49.2
unnamed: I2C_PU12.3, R50.2
unnamed: D13.A, R51.1
unnamed: D13.C, LED12.2
unnamed: I2C_PU13.1, R53.2
unnamed: I2C_PU13.3, R54.2
unnamed: D14.A, R55.1
unnamed: D14.C, LED13.2
unnamed: I2C_PU14.1, R57.2
unnamed: I2C_PU14.3, R58.2
unnamed: D15.A, R59.1
unnamed: D15.C, LED14.2
unnamed: I2C_PU15.1, R61.2
unnamed: I2C_PU15.3, R62.2
unnamed: D16.A, R63.1
unnamed: D16.C, LED15.2
unnamed: I2C_PU16.1, R65.2
unnamed: I2C_PU16.3, R66.2
unnamed: D17.A, R67.1
unnamed: D17.C, LED16.2
unnamed: I2C_PU17.1, R69.2
unnamed: I2C_PU17.3, R70.2
unnamed: D18.A, R71.1
unnamed: D18.C, LED17.2
unnamed: I2C_PU18.1, R73.2
unnamed: I2C_PU18.3, R74.2
unnamed: D19.A, R75.1
unnamed: D19.C, LED18.2
unnamed: I2C_PU19.1, R77.2
unnamed: I2C_PU19.3, R78.2
unnamed: D20.A, R79.1
unnamed: D20.C, LED19.2
unnamed: I2C_PU20.1, R81.2
unnamed: I2C_PU20.3, R82.2
unnamed: D21.A, R83.1
unnamed: D21.C, LED20.2
unnamed: I2C_PU21.1, R85.2
unnamed: I2C_PU21.3, R86.2
unnamed: D22.A, R87.1
unnamed: D22.C, LED21.2
unnamed: I2C_PU22.1, R89.2
unnamed: I2C_PU22.3, R90.2
unnamed: D23.A, R91.1
unnamed: D23.C, LED22.2
unnamed: I2C_PU23.1, R93.2
unnamed: I2C_PU23.3, R94.2
unnamed: D24.A, R95.1
unnamed: D24.C, LED23.2
unnamed: I2C_PU24.1, R97.2
unnamed: I2C_PU24.3, R98.2
unnamed: D25.A, R99.1
unnamed: D25.C, LED24.2
unnamed: I2C_PU25.1, R101.2
unnamed: I2C_PU25.3, R102.2
unnamed: D26.A, R103.1
unnamed: D26.C, LED25.2
unnamed: I2C_PU26.1, R105.2
unnamed: I2C_PU26.3, R106.2
unnamed: D27.A, R107.1
unnamed: D27.C, LED26.2
unnamed: I2C_PU27.1, R109.2
unnamed: I2C_PU27.3, R110.2
unnamed: D28.A, R111.1
unnamed: D28.C, LED27.2
unnamed: I2C_PU28.1, R113.2
unnamed: I2C_PU28.3, R114.2
unnamed: D29.A, R115.1
unnamed: D29.C, LED28.2
unnamed: I2C_PU29.1, R117.2
unnamed: I2C_PU29.3, R118.2
unnamed: D30.A, R119.1
unnamed: D30.C, LED29.2
unnamed: I2C_PU30.1, R121.2
unnamed: I2C_PU30.3, R122.2
unnamed: D31.A, R123.1
unnamed: D31.C, LED30.2
unnamed: I2C_PU31.1, R125.2
unnamed: I2C_PU31.3, R126.2
unnamed: D32.A, R127.1
unnamed: D32.C, LED31.2
unnamed: I2C_PU32.1, R129.2
unnamed: I2C_PU32.3, R130.2
unnamed: D33.A, R131.1
unnamed: D33.C, LED32.2
unnamed: I2C_PU33.1, R133.2
unnamed: I2C_PU33.3, R134.2
unnamed: D34.A, R135.1
unnamed: D34.C, LED33.2
unnamed: I2C_PU34.1, R137.2
unnamed: I2C_PU34.3, R138.2
unnamed: D35.A, R139.1
unnamed: D35.C, LED34.2
unnamed: I2C_PU35.1, R141.2
unnamed: I2C_PU35.3, R142.2
unnamed: D36.A, R143.1
unnamed: D36.C, LED35.2
unnamed: I2C_PU36.1, R145.2
unnamed: I2C_PU36.3, R146.2
unnamed: D37.A, R147.1
unnamed: D37.C, LED36.2
unnamed: I2C_PU37.1, R149.2
unnamed: I2C_PU37.3, R150.2
unnamed: D38.A, R151.1
unnamed: D38.C, LED37.2
unnamed: I2C_PU38.1, R153.2
unnamed: I2C_PU38.3, R154.2
unnamed: D39.A, R155.1
unnamed: D39.C, LED38.2
unnamed: I2C_PU39.1, R157.2
unnamed: I2C_PU39.3, R158.2
unnamed: D40.A, R159.1
unnamed: D40.C, LED39.2
unnamed: I2C_PU40.1, R161.2
unnamed: I2C_PU40.3, R162.2
unnamed: D41.A, R163.1
unnamed: D41.C, LED40.2
unnamed: I2C_PU41.1, R165.2
unnamed: I2C_PU41.3, R166.2
unnamed: D42.A, R167.1
unnamed: D42.C, LED41.2
unnamed: I2C_PU42.1, R169.2
unnamed: I2C_PU42.3, R170.2
unnamed: D43.A, R171.1
unnamed: D43.C, LED42.2
unnamed: I2C_PU43.1, R173.2
unnamed: I2C_PU43.3, R174.2
unnamed: D44.A, R175.1
unnamed: D44.C, LED43.2
unnamed: I2C_PU44.1, R177.2
unnamed: I2C_PU44.3, R178.2
unnamed: D45.A, R179.1
unnamed: D45.C, LED44.2
unnamed: I2C_PU45.1, R181.2
unnamed: I2C_PU45.3, R182.2
unnamed: D46.A, R183.1
unnamed: D46.C, LED45.2
unnamed: I2C_PU46.1, R185.2
unnamed: I2C_PU46.3, R186.2
unnamed: D47.A, R187.1
unnamed: D47.C, LED46.2
unnamed: I2C_PU47.1, R189.2
unnamed: I2C_PU47.3, R190.2
unnamed: D48.A, R191.1
unnamed: D48.C, LED47.2
unnamed: I2C_PU48.1, R193.2
unnamed: I2C_PU48.3, R194.2
unnamed: D49.A, R195.1
unnamed: D49.C, LED48.2
unnamed: I2C_PU49.1, R197.2
unnamed: I2C_PU49.3, R198.2
unnamed: D50.A, R199.1
unnamed: D50.C, LED49.2
unnamed: I2C_PU50.1, R201.2
unnamed: I2C_PU50.3, R202.2
unnamed: D51.A, R203.1
unnamed: D51.C, LED50.2
unnamed: I2C_PU51.1, R205.2
unnamed: I2C_PU51.3, R206.2
unnamed: D52.A, R207.1
unnamed: D52.C, LED51.2
unnamed: I2C_PU52.1, R209.2
unnamed: I2C_PU52.3, R210.2
unnamed: D53.A, R211.1
unnamed: D53.C, LED52.2
unnamed: I2C_PU53.1, R213.2
unnamed: I2C_PU53.3, R214.2
unnamed: D54.A, R215.1
unnamed: D54.C, LED53.2
unnamed: I2C_PU54.1, R217.2
unnamed: I2C_PU54.3, R218.2
unnamed: D55.A, R219.1
unnamed: D55.C, LED54.2
unnamed: I2C_PU55.1, R221.2
unnamed: I2C_PU55.3, R222.2
unnamed: D56.A, R223.1
unnamed: D56.C, LED55.2
unnamed: I2C_PU56.1, R225.2
unnamed: I2C_PU56.3, R226.2
unnamed: D57.A, R227.1
unnamed: D57.C, LED56.2
unnamed: I2C_PU57.1, R229.2
unnamed: I2C_PU57.3, R230.2
unnamed: D58.A, R231.1
unnamed: D58.C, LED57.2
unnamed: I2C_PU58.1, R233.2
unnamed: I2C_PU58.3, R234.2
unnamed: D59.A, R235.1
unnamed: D59.C, LED58.2
unnamed: I2C_PU59.1, R237.2
unnamed: I2C_PU59.3, R238.2
unnamed: D60.A, R239.1
unnamed: D60.C, LED59.2
unnamed: I2C_PU60.1, R241.2
unnamed: I2C_PU60.3, R242.2
unnamed: D61.A, R243.1
unnamed: D61.C, LED60.2
unnamed: I2C_PU61.1, R245.2
unnamed: I2C_PU61.3, R246.2
unnamed: D62.A, R247.1
unnamed: D62.C, LED61.2
unnamed: I2C_PU62.1, R249.2
unnamed: I2C_PU62.3, R250.2
unnamed: D63.A, R251.1
unnamed: D63.C, LED62.2
unnamed: I2C_PU63.1, R253.2
unnamed: I2C_PU63.3, R254.2
unnamed: D64.A, R255.1
unnamed: D64.C, LED63.2
SCL: J1.4, R1.1, TP3.1, U2.1
SCL1: J3.4, R3.1, TP7.1, U1.1
SCL2: J7.4, R9.1, TP11.1, U3.1
SCL3: J10.4, R13.1, TP15.1, U4.1
SCL4: J13.4, R17.1, TP19.1, U5.1
SCL5: J16.4, R21.1, TP23.1, U6.1
SCL6: J19.4, R25.1, TP27.1, U7.1
SCL7: J22.4, R29.1, TP31.1, U8.1
SCL8: J25.4, R33.1, TP35.1, U9.1
SCL9: J28.4, R37.1, TP39.1, U10.1
SCL10: J31.4, R41.1, TP43.1, U11.1
SCL11: J34.4, R45.1, TP47.1, U12.1
SCL12: J37.4, R49.1, TP51.1, U13.1
SCL13: J40.4, R53.1, TP55.1, U14.1
SCL14: J43.4, R57.1, TP59.1, U15.1
SCL15: J46.4, R61.1, TP63.1, U16.1
SCL16: J49.4, R65.1, TP67.1, U17.1
SCL17: J52.4, R69.1, TP71.1, U18.1
SCL18: J55.4, R73.1, TP75.1, U19.1
SCL19: J58.4, R77.1, TP79.1, U20.1
SCL20: J61.4, R81.1, TP83.1, U21.1
SCL21: J64.4, R85.1, TP87.1, U22.1
SCL22: J67.4, R89.1, TP91.1, U23.1
SCL23: J70.4, R93.1, TP95.1, U24.1
SCL24: J73.4, R97.1, TP99.1, U25.1
SCL25: J76.4, R101.1, TP103.1, U26.1
SCL26: J79.4, R105.1, TP107.1, U27.1
SCL27: J82.4, R109.1, TP111.1, U28.1
SCL28: J85.4, R113.1, TP115.1, U29.1
SCL29: J88.4, R117.1, TP119.1, U30.1
SCL30: J91.4, R121.1, TP123.1, U31.1
SCL31: J94.4, R125.1, TP127.1, U32.1
SCL32: J97.4, R129.1, TP131.1, U33.1
SCL33: J100.4, R133.1, TP135.1, U34.1
SCL34: J103.4, R137.1, TP139.1, U35.1
SCL35: J106.4, R141.1, TP143.1, U36.1
SCL36: J109.4, R145.1, TP147.1, U37.1
SCL37: J112.4, R149.1, TP151.1, U38.1
SCL38: J115.4, R153.1, TP155.1, U39.1
SCL39: J118.4, R157.1, TP159.1, U40.1
SCL40: J121.4, R161.1, TP163.1, U41.1
SCL41: J124.4, R165.1, TP167.1, U42.1
SCL42: J127.4, R169.1, TP171.1, U43.1
SCL43: J130.4, R173.1, TP175.1, U44.1
SCL44: J133.4, R177.1, TP179.1, U45.1
SCL45: J136.4, R181.1, TP183.1, U46.1
SCL46: J139.4, R185.1, TP187.1, U47.1
SCL47: J142.4, R189.1, TP191.1, U48.1
SCL48: J145.4, R193.1, TP195.1, U49.1
SCL49: J148.4, R197.1, TP199.1, U50.1
SCL50: J151.4, R201.1, TP203.1, U51.1
SCL51: J154.4, R205.1, TP207.1, U52.1
SCL52: J157.4, R209.1, TP211.1, U53.1
SCL53: J160.4, R213.1, TP215.1, U54.1
SCL54: J163.4, R217.1, TP219.1, U55.1
SCL55: J166.4, R221.1, TP223.1, U56.1
SCL56: J169.4, R225.1, TP227.1, U57.1
SCL57: J172.4, R229.1, TP231.1, U58.1
SCL58: J175.4, R233.1, TP235.1, U59.1
SCL59: J178.4, R237.1, TP239.1, U60.1
SCL60: J181.4, R241.1, TP243.1, U61.1
SCL61: J184.4, R245.1, TP247.1, U62.1
SCL62: J187.4, R249.1, TP251.1, U63.1
SCL63: J190.4, R253.1, TP255.1, U64.1
SDA: J1.3, R2.1, TP2.1, U2.16
SDA1: J3.3, R5.1, TP6.1, U1.16
SDA2: J7.3, R10.1, TP10.1, U3.16
SDA3: J10.3, R14.1, TP14.1, U4.16
SDA4: J13.3, R18.1, TP18.1, U5.16
SDA5: J16.3, R22.1, TP22.1, U6.16
SDA6: J19.3, R26.1, TP26.1, U7.16
SDA7: J22.3, R30.1, TP30.1, U8.16
SDA8: J25.3, R34.1, TP34.1, U9.16
SDA9: J28.3, R38.1, TP38.1, U10.16
SDA10: J31.3, R42.1, TP42.1, U11.16
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

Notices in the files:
parts and their libraries:
SparkFun-Aesthetics: Licensing: Creative Commons ShareAlike 4.0 International - https://creativecommons.org/licenses/by-sa/4.0
SparkFun-Aesthetics: Released under the Creative Commons Attribution Share-Alike 4.0 License
SparkFun-Aesthetics: https://creativecommons.org/licenses/by-sa/4.0
